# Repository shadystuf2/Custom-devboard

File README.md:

# RP2040 Devboard
This is a devboard with an accelerometer/gyroscope and an RP2040 MCU. The design was made using KiCad.  

This project is for HORIZONS EUROPA  

Steps taken and the whole work process is logged in JOURNAL.md

**Time taken: 13h**

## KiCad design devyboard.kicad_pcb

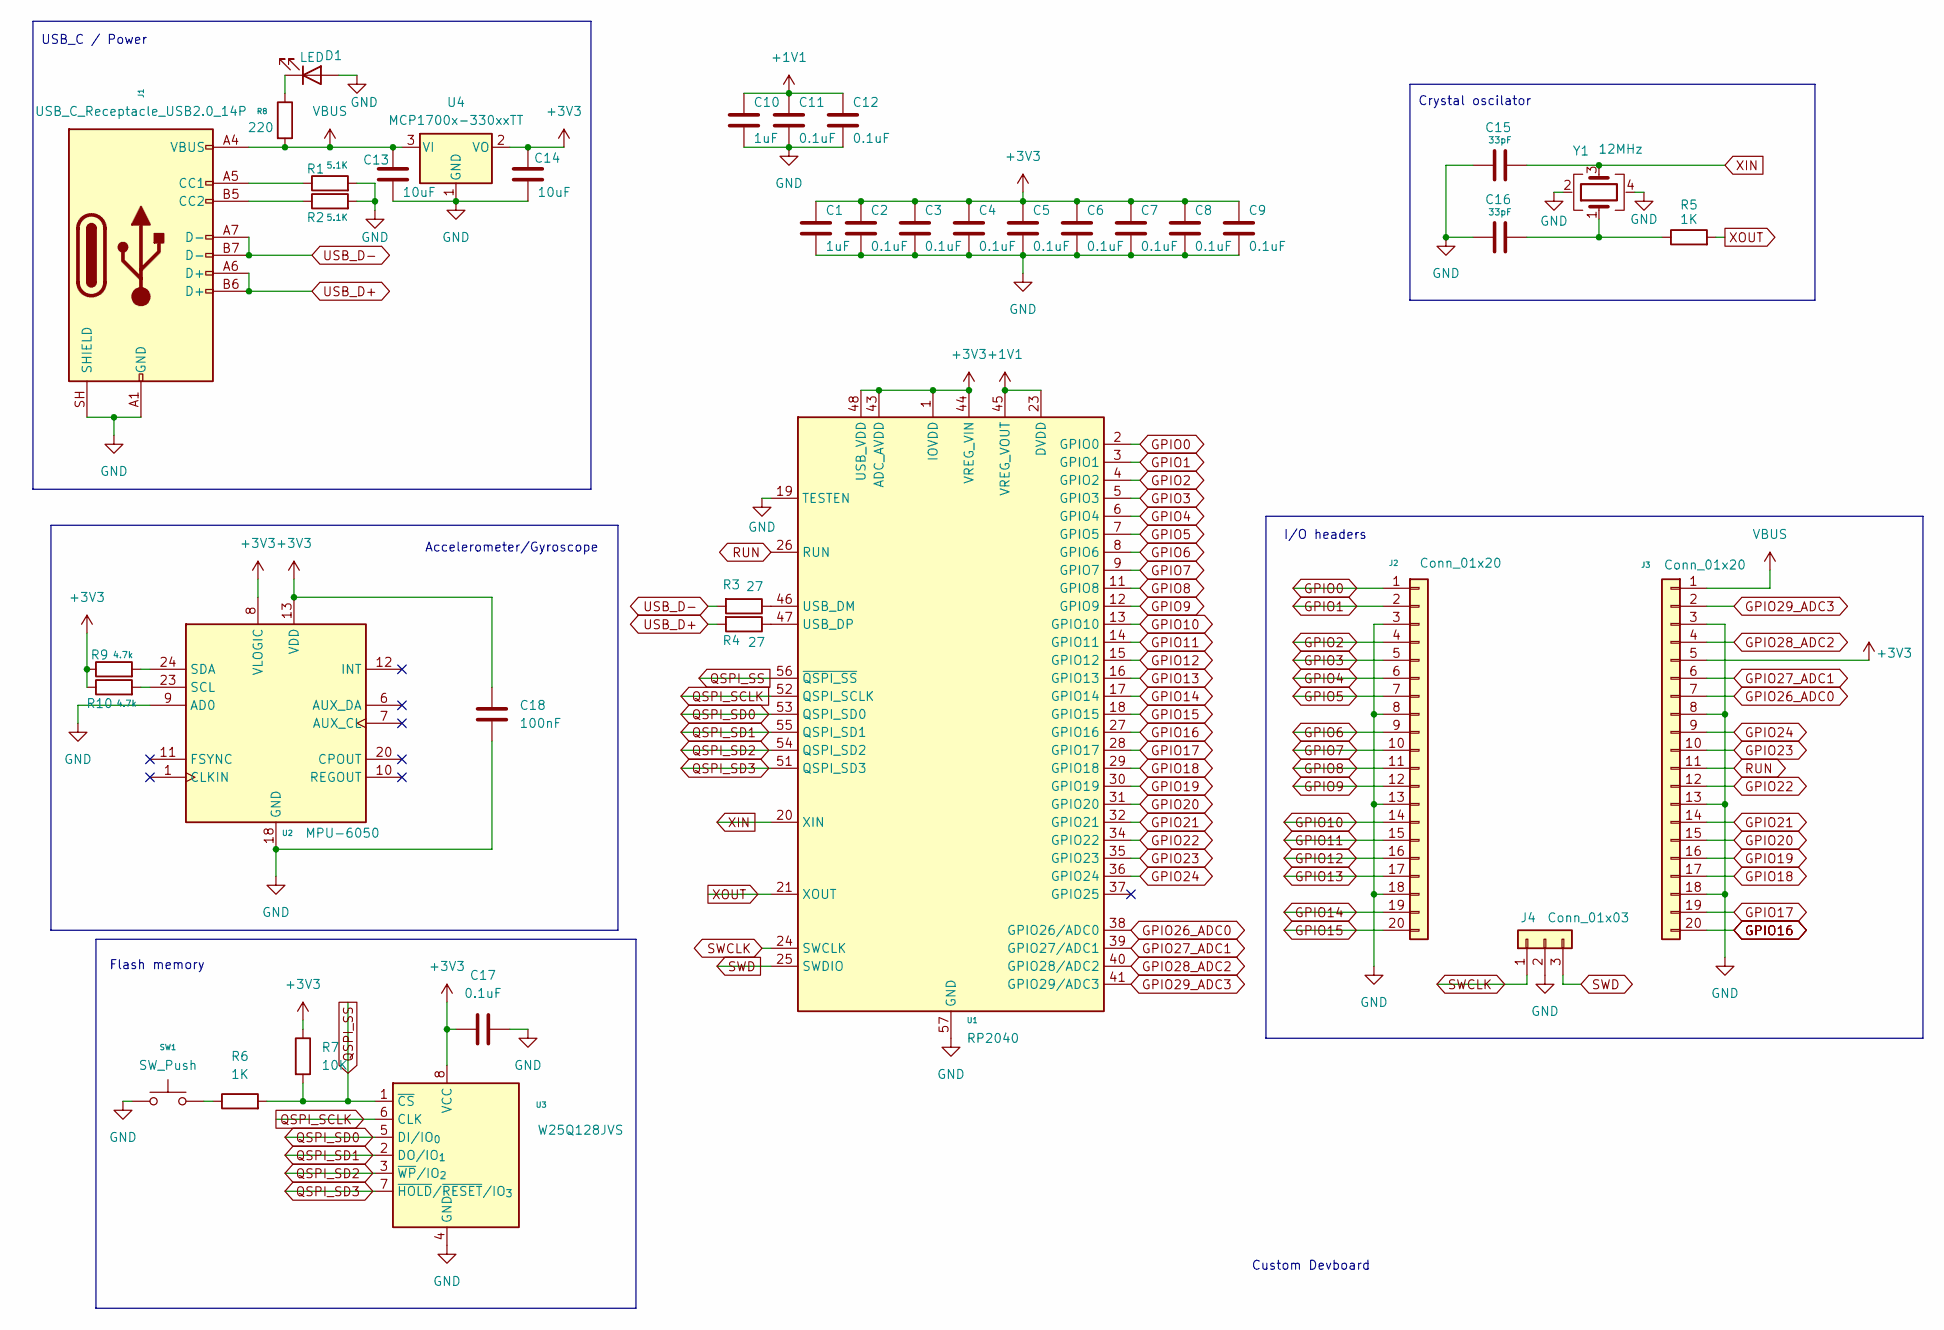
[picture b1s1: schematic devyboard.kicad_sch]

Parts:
C1, C10: 1uF; C_0402_1005Metric
C2, C3, C4, C5, C6, C7, C8, C9, C11, C12, C17: 0.1uF; C_0402_1005Metric
C13, C14: 10uF; C_0603_1608Metric
C15, C16: 33pF; C_0402_1005Metric
C18: 100nF; C_0402_1005Metric
D1: LED; LED_0603_1608Metric
J1: USB_C_Receptacle_USB2.0_14P; USB_C_Receptacle_HRO_TYPE-C-31-M-12
J2, J3: Conn_01x20; PinHeader_1x20_P2.54mm_Vertical
J4: Conn_01x03; PinHeader_1x03_P2.54mm_Vertical
R1, R2: 5.1K; R_0402_1005Metric
R3, R4: 27; R_0402_1005Metric
R5, R6: 1K; R_0402_1005Metric
R7: 10K; R_0402_1005Metric
R8: 220; R_0402_1005Metric
R9, R10: 4.7k; R_0402_1005Metric
SW1: SW_Push; SW_Push_SPST_NO_Alps_SKRK
U1: RP2040; QFN-56-1EP_7x7mm_P0.4mm_EP3.2x3.2mm
U2: MPU-6050; InvenSense_QFN-24_4x4mm_P0.5mm
U3: W25Q128JVS; Winbond_USON-8-1EP_3x2mm_P0.5mm_EP0.2x1.6mm
U4: MCP1700x-330xxTT; SOT-23
Y1: 12MHz; Crystal_SMD_3225-4Pin_3.2x2.5mm

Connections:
+1V1: C10.1, C11.1, C12.1, U1.23 (DVDD), U1.45 (VREG_VOUT), U1.50 (DVDD)
+3V3: C1.1, C2.1, C3.1, C4.1, C5.1, C6.1, C7.1, C8.1, C9.1, C14.1, C17.2, C18.1, J3.5, R7.1, R9.1, R10.1, U1.1 (IOVDD), U1.10 (IOVDD), U1.22 (IOVDD), U1.33 (IOVDD), U1.42 (IOVDD), U1.43 (ADC_AVDD), U1.44 (VREG_VIN), U1.48 (USB_VDD), U1.49 (IOVDD), U2.8 (VLOGIC), U2.13 (VDD), U3.8 (VCC), U4.2 (VO)
GND: C1.2, C2.2, C3.2, C4.2, C5.2, C6.2, C7.2, C8.2, C9.2, C10.2, C11.2, C12.2, C13.2, C14.2, C15.1, C16.1, C17.1, C18.2, D1.2 (A), J1.A1 (GND), J1.A12 (GND), J1.B1 (GND), J1.B12 (GND), J1.SH (SHIELD), J2.3, J2.8, J2.13, J2.18, J3.3, J3.8, J3.13, J3.18, J4.2, R1.2, R2.2, SW1.1, U1.19 (TESTEN), U1.57 (GND), U2.9 (AD0), U2.18 (GND), U3.4 (GND), U4.1 (GND), Y1.2 (G), Y1.4 (G)
GPIO0: J2.1, U1.2 (GPIO0)
GPIO1: J2.2, U1.3 (GPIO1)
GPIO2: J2.4, U1.4 (GPIO2)
GPIO3: J2.5, U1.5 (GPIO3)
GPIO4: J2.6, U1.6 (GPIO4)
GPIO5: J2.7, U1.7 (GPIO5)
GPIO6: J2.9, U1.8 (GPIO6)
GPIO7: J2.10, U1.9 (GPIO7)
GPIO8: J2.11, U1.11 (GPIO8)
GPIO9: J2.12, U1.12 (GPIO9)
GPIO10: J2.14, U1.13 (GPIO10)
GPIO11: J2.15, U1.14 (GPIO11)
GPIO12: J2.16, U1.15 (GPIO12)
GPIO13: J2.17, U1.16 (GPIO13)
GPIO14: J2.19, U1.17 (GPIO14)
GPIO15: J2.20, U1.18 (GPIO15)
GPIO16: J3.20, U1.27 (GPIO16)
GPIO17: J3.19, U1.28 (GPIO17)
GPIO18: J3.17, U1.29 (GPIO18)
GPIO19: J3.16, U1.30 (GPIO19)
GPIO20: J3.15, U1.31 (GPIO20)
GPIO21: J3.14, U1.32 (GPIO21)
GPIO22: J3.12, U1.34 (GPIO22)
GPIO23: J3.10, U1.35 (GPIO23)
GPIO24: J3.9, U1.36 (GPIO24)
GPIO26_ADC0: J3.7, U1.38 (GPIO26/ADC0)
GPIO27_ADC1: J3.6, U1.39 (GPIO27/ADC1)
GPIO28_ADC2: J3.4, U1.40 (GPIO28/ADC2)
GPIO29_ADC3: J3.2, U1.41 (GPIO29/ADC3)
unnamed: C16.2, R5.1, Y1.1
unnamed: D1.1 (K), R8.1
unnamed: J1.A5 (CC1), R1.1
unnamed: J1.B5 (CC2), R2.1
unnamed: R6.1, SW1.2
unnamed: R3.1, U1.46 (USB_DM)
unnamed: R4.1, U1.47 (USB_DP)
unnamed: R10.2, U2.23 (SCL)
unnamed: R9.2, U2.24 (SDA)
QSPI_SCLK: U1.52 (QSPI_SCLK), U3.6 (CLK)
QSPI_SD0: U1.53 (QSPI_SD0), U3.5 (DI/IO_{0})
QSPI_SD1: U1.55 (QSPI_SD1), U3.2 (DO/IO_{1})
QSPI_SD2: U1.54 (QSPI_SD2), U3.3 (~WP/IO_{2})
QSPI_SD3: U1.51 (QSPI_SD3), U3.7 (~HOLD/~RESET/IO_{3})
QSPI_SS: R6.2, R7.2, U1.56 (~QSPI_SS), U3.1 (~CS)
RUN: J3.11, U1.26 (RUN)
SWCLK: J4.1, U1.24 (SWCLK)
SWD: J4.3, U1.25 (SWDIO)
USB_D+: J1.A6 (D+), J1.B6 (D+), R4.2
USB_D-: J1.A7 (D-), J1.B7 (D-), R3.2
VBUS: C13.1, J1.A4 (VBUS), J1.A9 (VBUS), J1.B4 (VBUS), J1.B9 (VBUS), J3.1, R8.2, U4.3 (VI)
XIN: C15.2, U1.20 (XIN), Y1.3
XOUT: R5.2, U1.21 (XOUT)

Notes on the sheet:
I/O headers
Flash memory
USB_C / Power
Accelerometer/Gyroscope
Crystal oscilator
Custom Devboard

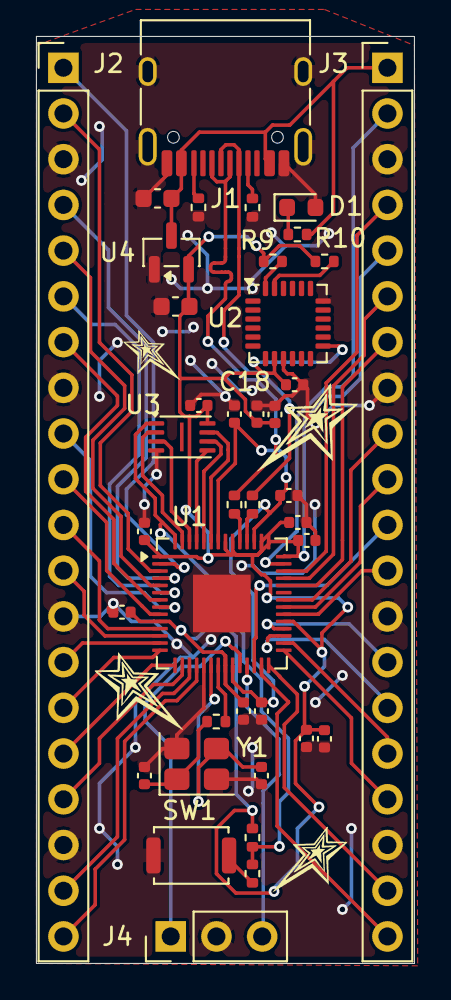
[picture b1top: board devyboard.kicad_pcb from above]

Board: 2 copper layers, 21.0 x 51.5 mm, 39 parts (0 on the bottom side), 55 nets.

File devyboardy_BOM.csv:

"Reference","Qty","Value","DNP","Exclude from BOM","Exclude from Board","Footprint","Datasheet"
"C1,C10","2","1uF","","","","Capacitor_SMD:C_0402_1005Metric",""
"C2,C3,C4,C5,C6,C7,C8,C9,C11,C12,C17","11","0.1uF","","","","Capacitor_SMD:C_0402_1005Metric",""
"C13,C14","2","10uF","","","","Capacitor_SMD:C_0603_1608Metric",""
"C15,C16","2","33pF","","","","Capacitor_SMD:C_0402_1005Metric",""
"C18","1","100nF","","","","Capacitor_SMD:C_0402_1005Metric",""
"D1","1","LED","","","","LED_SMD:LED_0603_1608Metric",""
"J1","1","USB_C_Receptacle_USB2.0_14P","","","","Connector_USB:USB_C_Receptacle_HRO_TYPE-C-31-M-12","https://www.usb.org/sites/default/files/documents/usb_type-c.zip"
"J2,J3","2","Conn_01x20","","","","Connector_PinHeader_2.54mm:PinHeader_1x20_P2.54mm_Vertical",""
"J4","1","Conn_01x03","","","","Connector_PinHeader_2.54mm:PinHeader_1x03_P2.54mm_Vertical",""
"R1,R2","2","5.1K","","","","Resistor_SMD:R_0402_1005Metric",""
"R3,R4","2","27","","","","Resistor_SMD:R_0402_1005Metric",""
"R5,R6","2","1K","","","","Resistor_SMD:R_0402_1005Metric",""
"R7","1","10K","","","","Resistor_SMD:R_0402_1005Metric",""
"R8","1","220","","","","Resistor_SMD:R_0402_1005Metric",""
"R9,R10","2","4.7k","","","","Resistor_SMD:R_0402_1005Metric",""
"SW1","1","SW_Push","","","","Button_Switch_SMD:SW_Push_SPST_NO_Alps_SKRK",""
"U1","1","RP2040","","","","Package_DFN_QFN:QFN-56-1EP_7x7mm_P0.4mm_EP3.2x3.2mm","https://datasheets.raspberrypi.com/rp2040/rp2040-datasheet.pdf"
"U2","1","MPU-6050","","","","Sensor_Motion:InvenSense_QFN-24_4x4mm_P0.5mm","https://invensense.tdk.com/wp-content/uploads/2015/02/MPU-60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"
"U3","1","W25Q128JVS","","","","Package_SON:Winbond_USON-8-1EP_3x2mm_P0.5mm_EP0.2x1.6mm","https://www.winbond.com/resource-files/w25q128jv_dtr%20revc%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"
"U4","1","MCP1700x-330xxTT","","","","Package_TO_SOT_SMD:SOT-23","http://ww1.microchip.com/downloads/en/DeviceDoc/20001826D.pdf"
"Y1","1","12MHz","","","","Crystal:Crystal_SMD_3225-4Pin_3.2x2.5mm",""
